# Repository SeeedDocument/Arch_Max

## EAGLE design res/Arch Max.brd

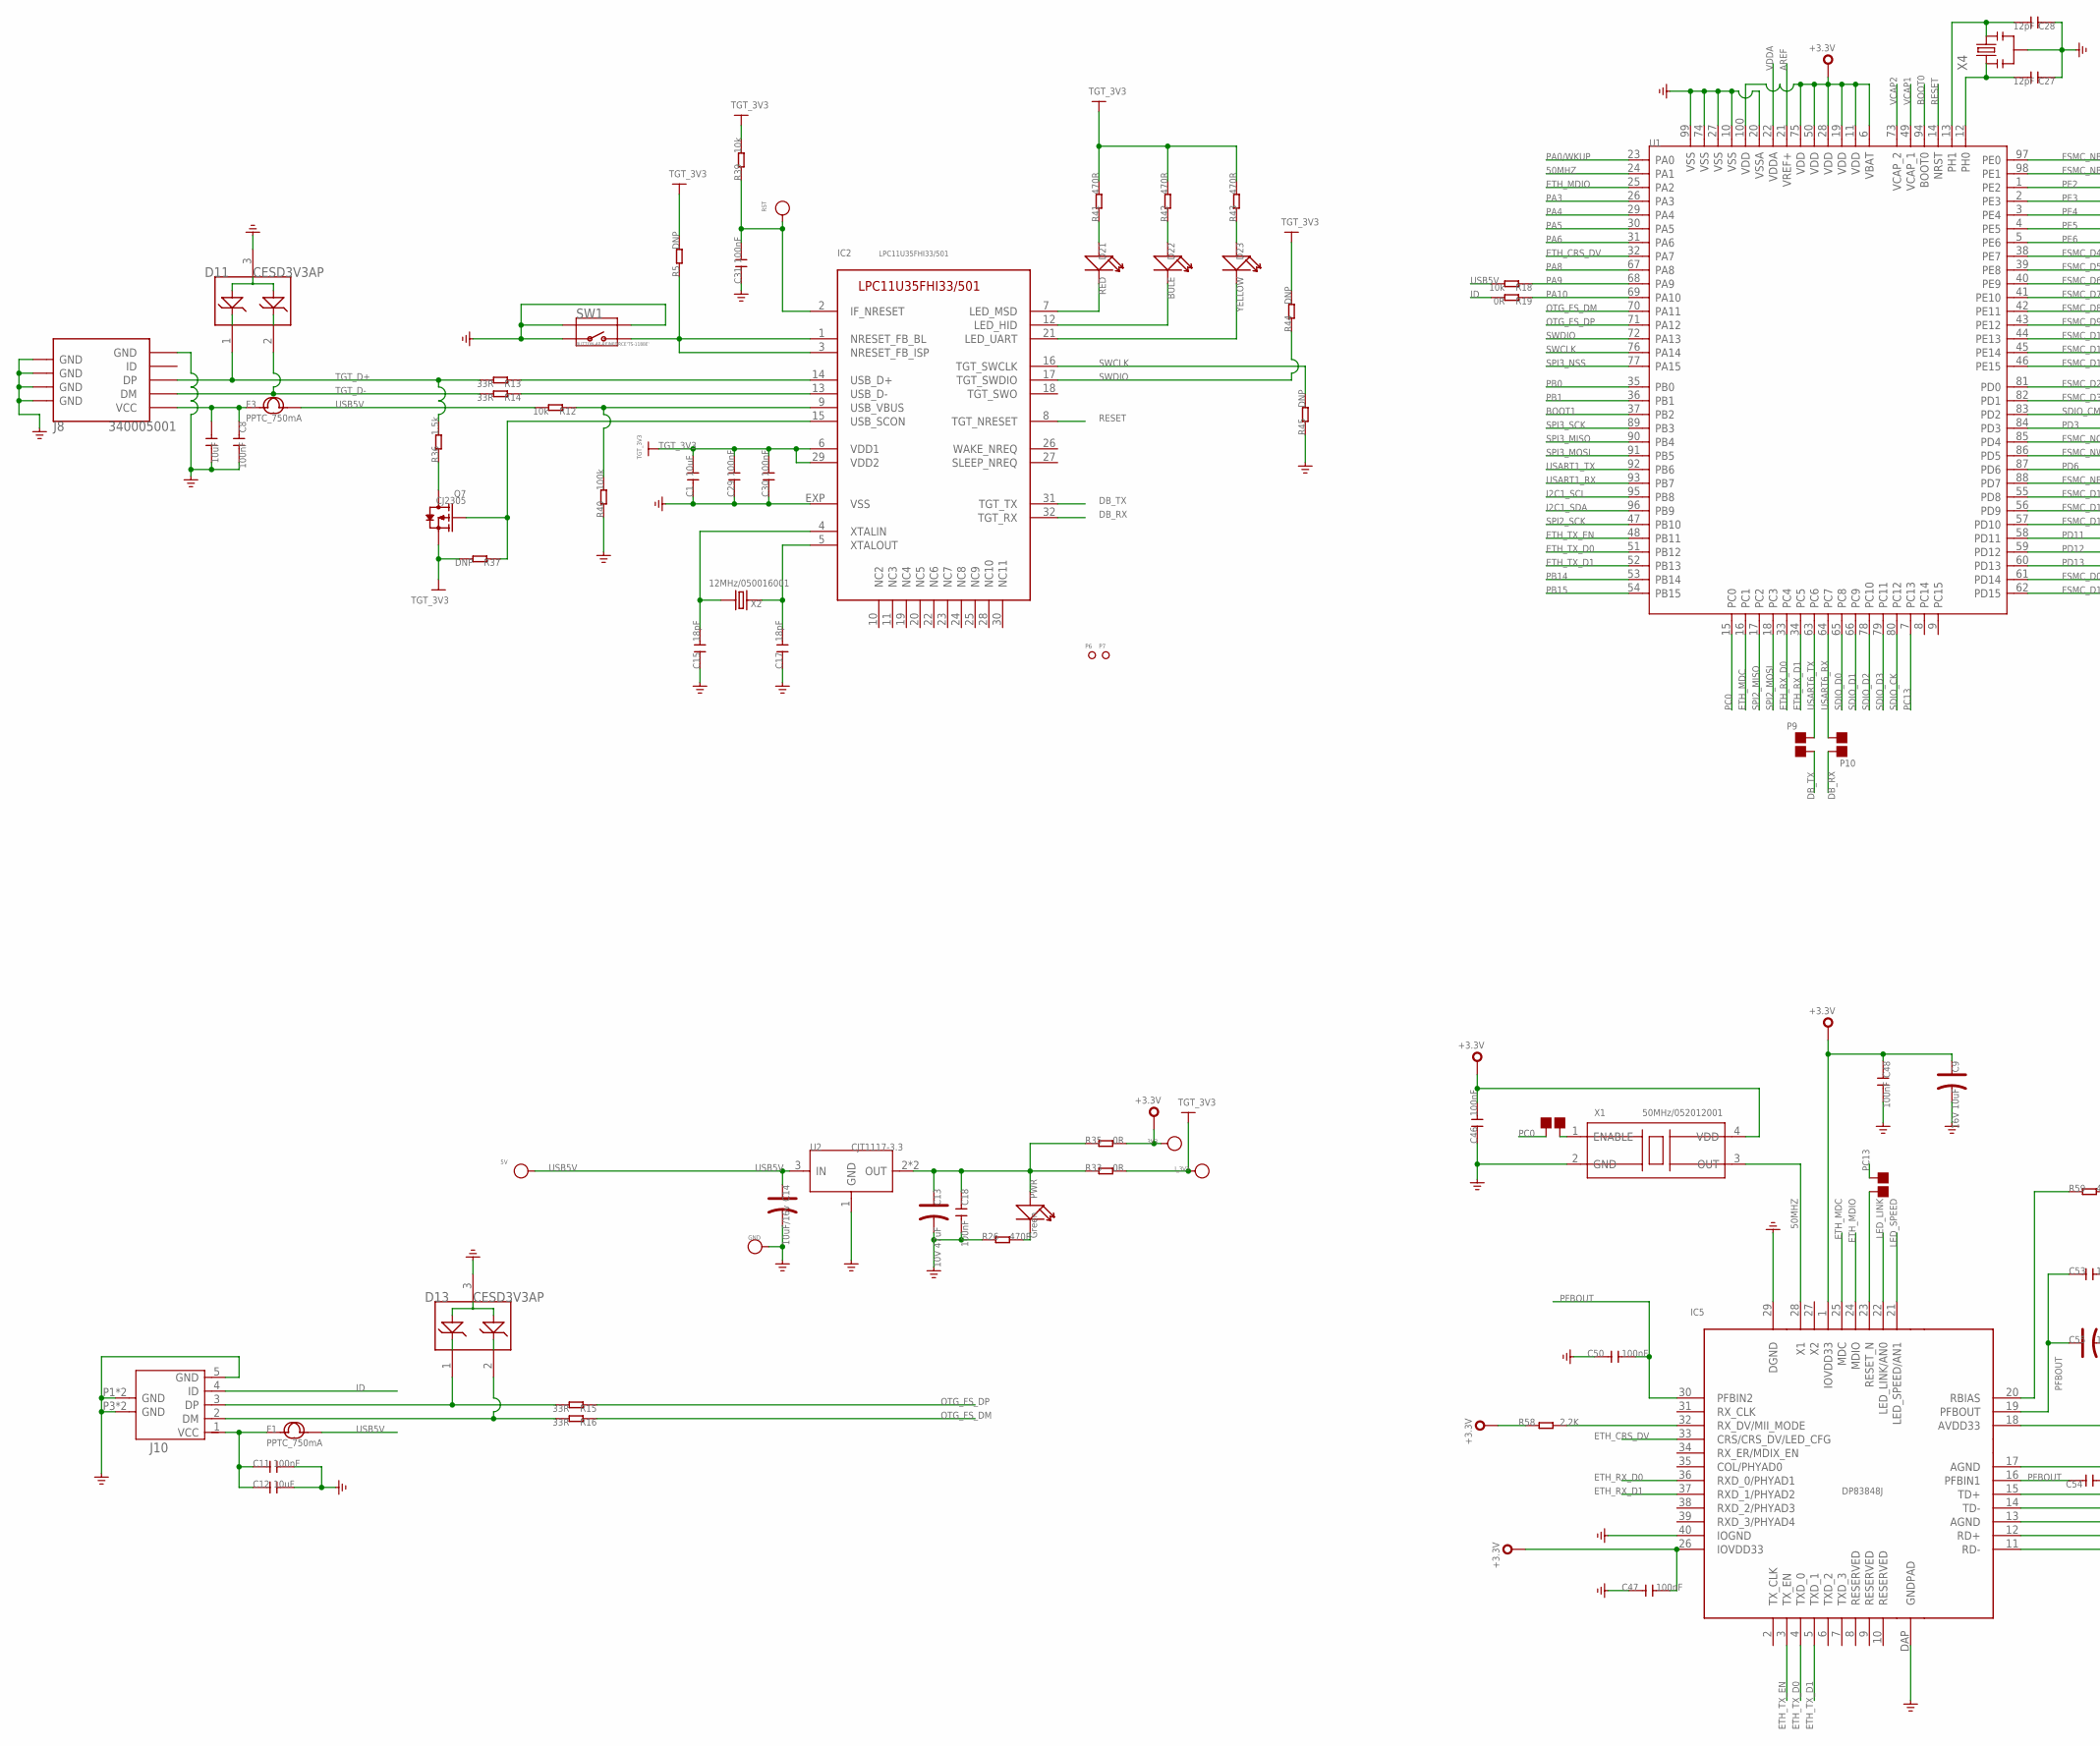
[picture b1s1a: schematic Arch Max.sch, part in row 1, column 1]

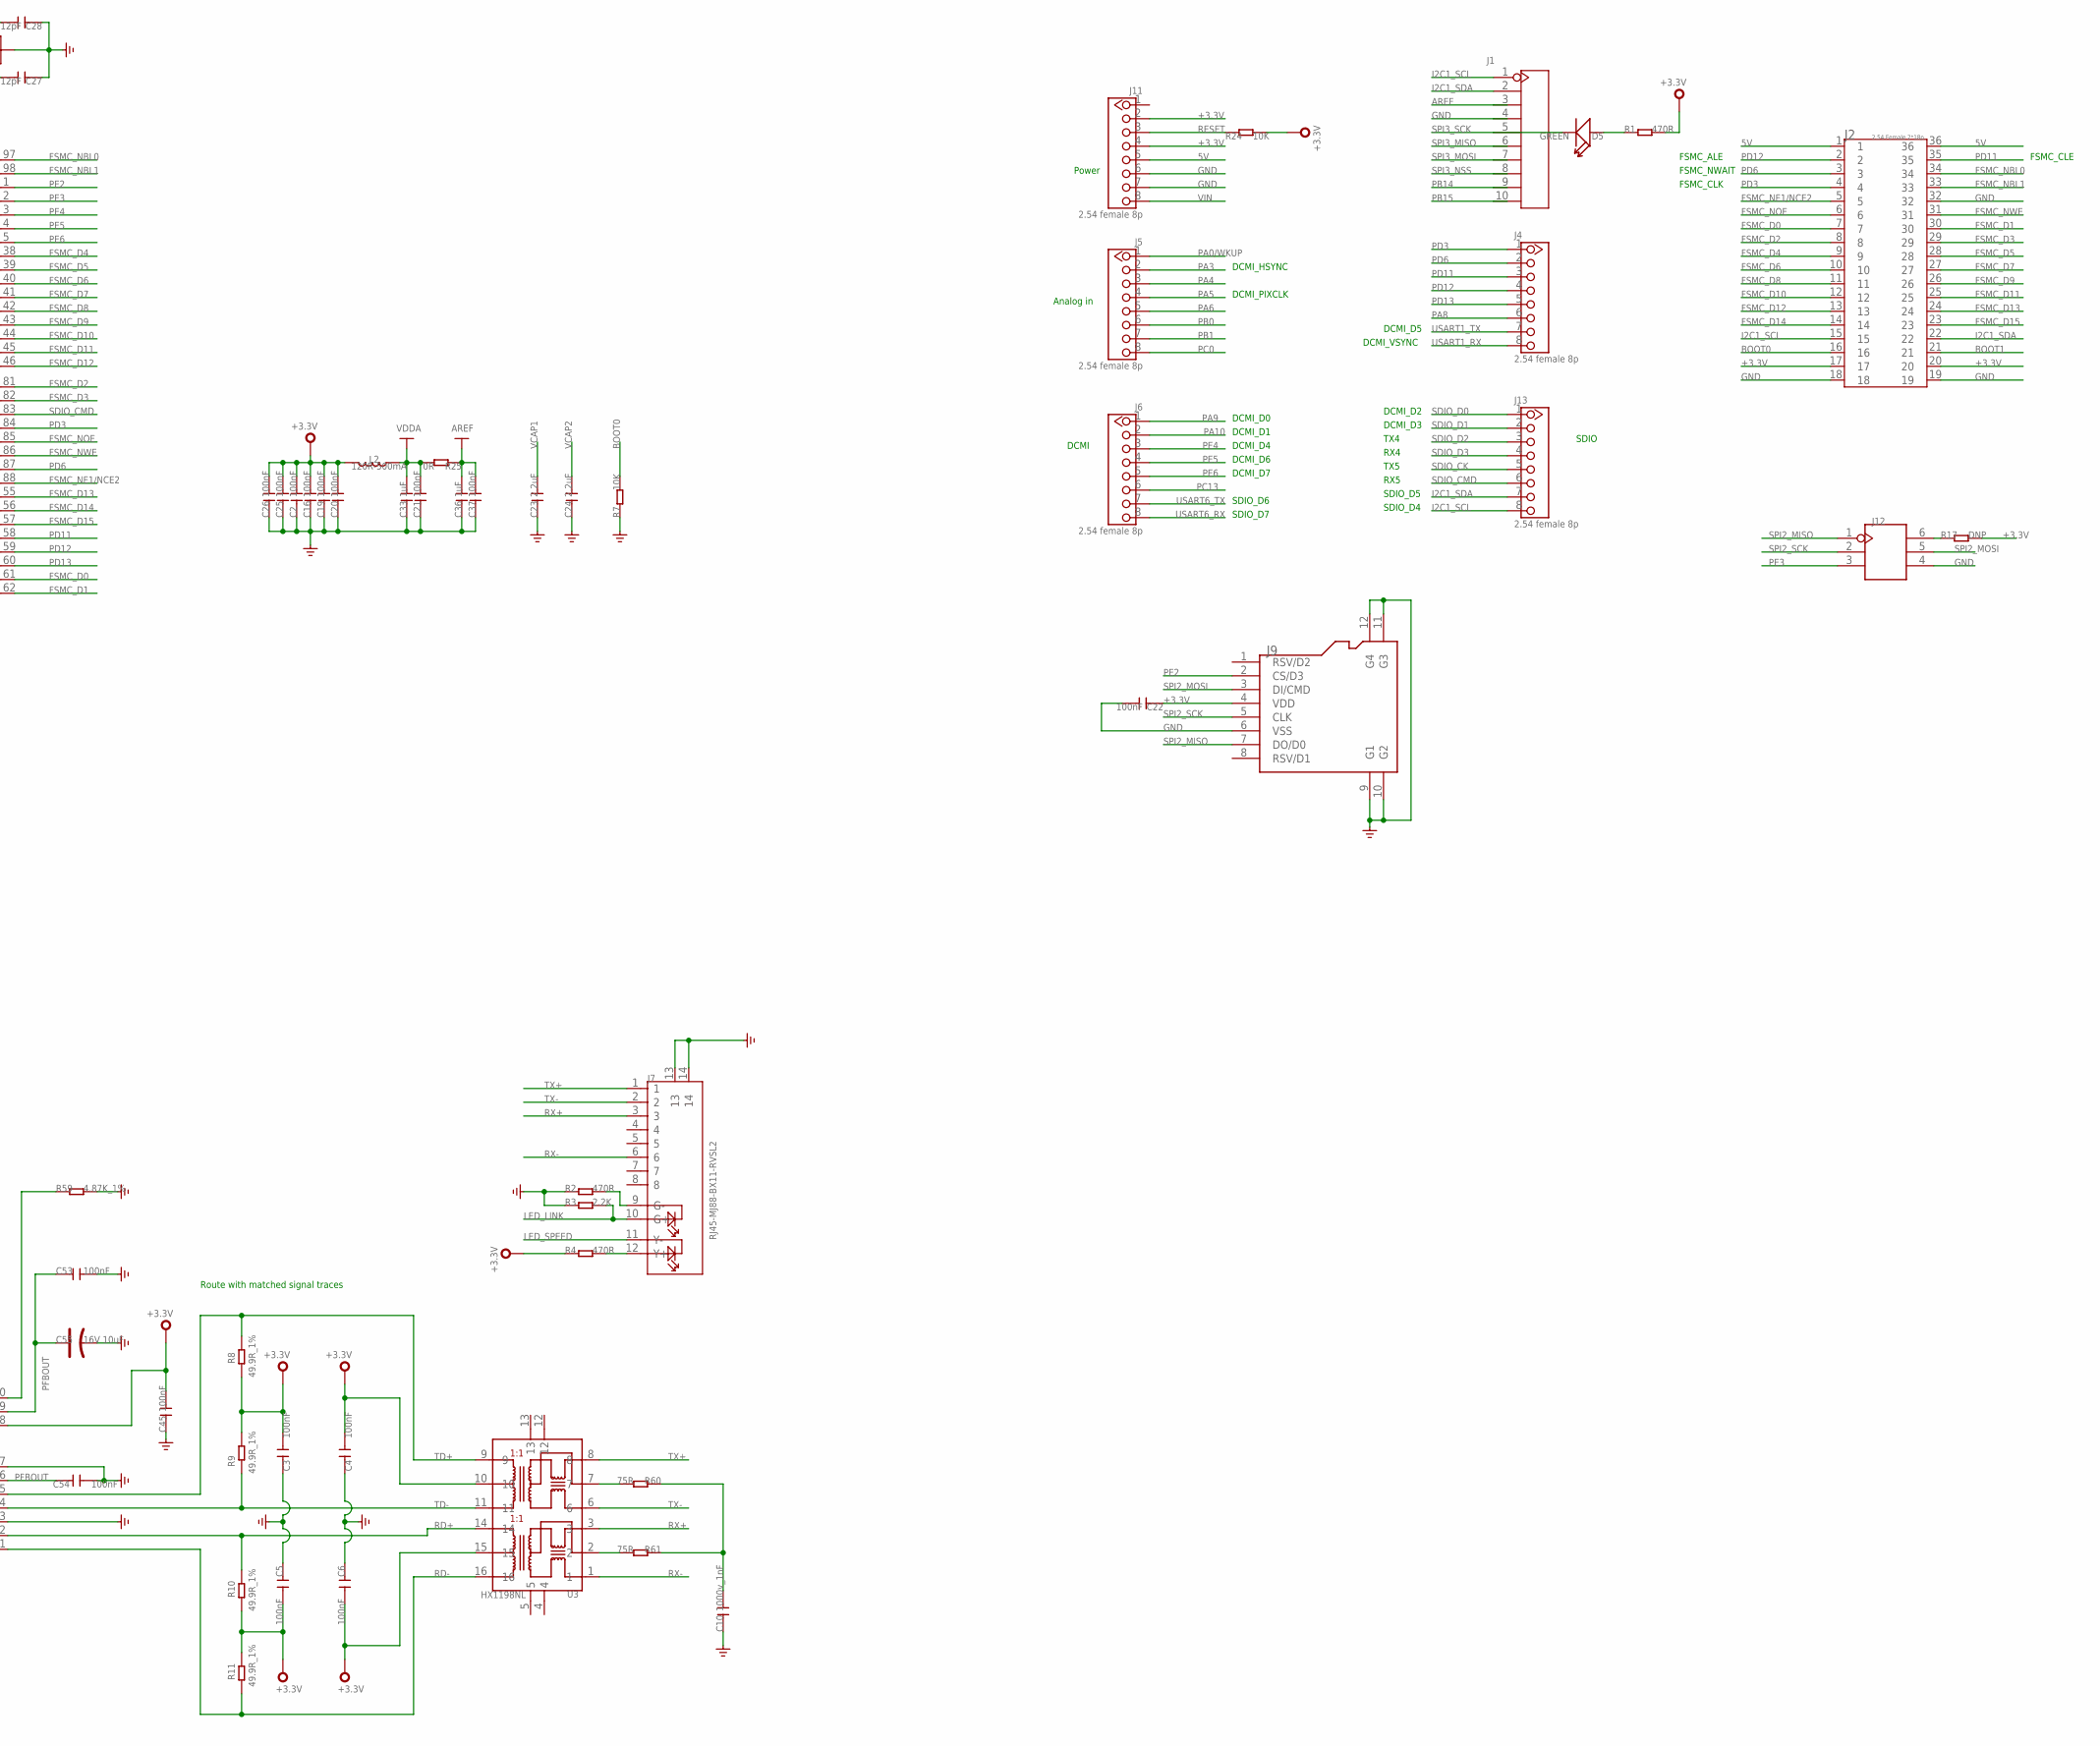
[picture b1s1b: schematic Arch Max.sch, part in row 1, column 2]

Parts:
3V3, 5V: PAD-TEST-POINT'4545'; TP_4545
C1, C7, C12: 10uF; C0805
C2, C3, C4, C5, C6, C8, C11, C16, C18, C19, C20, C21, C22, C25, C26, C29, C30, C31, C37, C45, C46, C47, C48, C50, C53, C54: 100nF; C0603
C9, C55: 16V 10uF; AVX-A
C10: 1000v_1nF; C1206
C13: 10V 47uF; AVX-B
C14: 10uF/16v; AVX-A
C15, C17: 18pF; C0603
C23, C24: 2.2uF; C0603
C27, C28: 12pF; C0603
C33, C36: 1uF; C0603
D5: GREEN; LED-0603
D11, D13: CESD3V3AP; SOT23
D21: RED; LED-0603
D22: BULE; LED-0603
D23: YELLOW; LED-0603
F1, F3: PPTC_750mA; F1206
GND: PAD-TEST-POINT'4545'; TP_4545
IC2: LPC11U35FHI33/501; MBED-ICS_HVQFN33
IC5: DP83848J; LLP-40
I_3V3: PAD-TEST-POINT'4545'; TP_4545
J1: HEADER-10P-2.54; 10P-2.54-65/35MIL
J2: 2.54 Female 2*18p; 2.54-2X18P
J4, J5, J6, J11, J13: 2.54 female 8p; CK_1X8
J7: RJ45-MJ88-BX11-RVSL2
J8: 340005001; MICRO-USB
J9: HOLDER-MICROSD-8P; 8P-SMD
J10: USB-MICRO-5P'AB'; MICRO-USB-5P-AB
J12: HEADER-2X3P-65/35MIL; 2X3P-2.54-65/35MIL
L2: 120R-500mA; L0603
P1, P5, P9, P10: PAD-JUMPER-2P; 2P-SMD-1.78X1.27
P6, P7: PAD-MARK'ANNULAR'; ROUND-MARK-1.0
PWR: Green; LED-0603
Q7: CJ2305; SOT23
R1, R2, R4, R26, R41, R42, R43: 470R; R0603
R3, R58: 2.2K; R0603
R5, R17, R37, R44, R45: DNP; R0603
R7, R24: 10K; R0603
R8, R9, R10, R11: 49.9R_1%; R0603
R12, R18, R39: 10k; R0603
R13, R14, R15, R16: 33R; R0603
R19, R25, R33, R35: 0R; R0603
R36: 1.5k; R0603
R40: 100k; R0603
R59: 4.87K_1%; R0603
R60, R61: 75R; R0603
RST: PAD-TEST-POINT'4545'; TP_4545
SW1: BUTTON-4P-REINFORCE'TS-1188E'; 4P-SMD-7X3.5X3.5H
U1: STM32F407VET6; LQFP100
U2: CJT1117-3.3; SOT-223
U3: HX1198NL; SOIC16-9.53
X1: 50MHz/052012001; 4P-SMD-5X3.2
X2: 12MHz/050016001; 2P-SMD-5X3.2
X4: CRYSTAL-RESONATOR'SMD'; 3P-SMD-3.6X1.3

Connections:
5V: J2.1, J2.36, J11.5
50MHZ: IC5.28 (X1), U1.24 (PA1), X1.3 (OUT)
+3.3V: 3V3.T, C2.2, C3.1, C4.1, C5.1, C6.1, C9.+, C16.2, C19.2, C20.2, C22.1, C25.2, C26.2, C45.2, C46.2, C47.1, C48.1, IC5.1 (IOVDD33), IC5.18 (AVDD33), IC5.26 (IOVDD33), J2.17, J2.20, J9.4 (VDD), J11.2, J11.4, L2.2, R1.2, R4.1, R8.1, R9.2, R10.1, R11.2, R17.2, R24.2, R35.1, R58.1, U1.6 (VBAT), U1.11 (VDD), U1.19 (VDD), U1.28 (VDD), U1.50 (VDD), U1.75 (VDD), U1.100 (VDD), U3.10, U3.15, X1.4 (VDD)
AREF: C36.2, C37.2, J1.3, R25.1, U1.21 (VREF+)
BOOT0: J2.16, R7.2, U1.94 (BOOT0)
BOOT1: J2.21, U1.37 (PB2)
DB_RX: IC2.32 (TGT_RX), P10.2
DB_TX: IC2.31 (TGT_TX), P9.1
ETH_CRS_DV: IC5.33 (CRS/CRS_DV/LED_CFG), U1.32 (PA7)
ETH_MDC: IC5.25 (MDC), U1.16 (PC1)
ETH_MDIO: IC5.24 (MDIO), U1.25 (PA2)
ETH_RX_D0: IC5.36 (RXD_0/PHYAD1), U1.33 (PC4)
ETH_RX_D1: IC5.37 (RXD_1/PHYAD2), U1.34 (PC5)
ETH_TX_D0: IC5.4 (TXD_0), U1.51 (PB12)
ETH_TX_D1: IC5.5 (TXD_1), U1.52 (PB13)
ETH_TX_EN: IC5.3 (TX_EN), U1.48 (PB11)
FSMC_D0: J2.7, U1.61 (PD14)
FSMC_D1: J2.30, U1.62 (PD15)
FSMC_D2: J2.8, U1.81 (PD0)
FSMC_D3: J2.29, U1.82 (PD1)
FSMC_D4: J2.9, U1.38 (PE7)
FSMC_D5: J2.28, U1.39 (PE8)
FSMC_D6: J2.10, U1.40 (PE9)
FSMC_D7: J2.27, U1.41 (PE10)
FSMC_D8: J2.11, U1.42 (PE11)
FSMC_D9: J2.26, U1.43 (PE12)
FSMC_D10: J2.12, U1.44 (PE13)
FSMC_D11: J2.25, U1.45 (PE14)
FSMC_D12: J2.13, U1.46 (PE15)
FSMC_D13: J2.24, U1.55 (PD8)
FSMC_D14: J2.14, U1.56 (PD9)
FSMC_D15: J2.23, U1.57 (PD10)
FSMC_NBL0: J2.34, U1.97 (PE0)
FSMC_NBL1: J2.33, U1.98 (PE1)
FSMC_NE1/NCE2: J2.5, U1.88 (PD7)
FSMC_NOE: J2.6, U1.85 (PD4)
FSMC_NWE: J2.31, U1.86 (PD5)
GND: C1.1, C2.1, C3.2, C4.2, C5.2, C6.2, C7.2, C8.2, C9.-, C10.1, C11.2, C12.2, C13.-, C14.-, C15.1, C16.1, C17.1, C18.1, C19.1, C20.1, C21.1, C22.2, C23.1, C24.1, C25.1, C26.1, C27.1, C28.1, C29.1, C30.1, C31.1, C33.1, C36.1, C37.1, C45.1, C46.1, C47.2, C48.2, C50.2, C53.1, C54.1, C55.-, D11.3, D13.3, GND.T, IC2.EXP (VSS), IC5.13 (AGND), IC5.17 (AGND), IC5.29 (DGND), IC5.40 (IOGND), IC5.DAP (GNDPAD), J1.4, J2.18, J2.19, J2.32, J7.13, J7.14, J8.5 (GND), J8.S1 (GND), J8.S2 (GND), J8.S3 (GND), J8.S4 (GND), J8.S5 (GND), J8.S6 (GND), J9.6 (VSS), J9.9 (G1), J9.10 (G2), J9.11 (G3), J9.12 (G4), J10.5 (GND), J10.P1 (GND), J10.P2 (GND), J10.P3 (GND), J10.P4 (GND), J11.6, J11.7, J12.4, R2.1, R3.1, R7.1, R26.1, R40.1, R45.1, R59.2, SW1.1, SW1.S1, SW1.S2, U1.10 (VSS), U1.20 (VSSA), U1.27 (VSS), U1.74 (VSS), U1.99 (VSS), U2.1 (GND), X1.2 (GND), X4.2
GREEN: D22.-, IC2.12 (LED_HID)
GREEN1: D21.-, IC2.7 (LED_MSD)
I2C1_SCL: J1.1, J2.15, J13.8, U1.95 (PB8)
I2C1_SDA: J1.2, J2.22, J13.7, U1.96 (PB9)
ID: J10.4 (ID), R19.2
LED_LINK: IC5.22 (LED_LINK/AN0), J7.10 (G+), R3.2
LED_SPEED: IC5.21 (LED_SPEED/AN1), J7.11 (Y-)
unnamed: C11.1, C12.1, F1.1, J10.1 (VCC)
unnamed: J12.6, R17.1
unnamed: IC2.1 (NRESET_FB_BL), IC2.3 (NRESET_FB_ISP), R5.1, SW1.2
unnamed: IC5.23 (RESET_N), P1.2
unnamed: IC2.9 (USB_VBUS), R12.1, R40.2
unnamed: J7.9 (G-), R2.2
unnamed: J7.12 (Y+), R4.2
unnamed: D5.+, R1.1
unnamed: P5.2, X1.1 (ENABLE)
unnamed: C7.1, C8.1, F3.1, J8.1 (VCC)
unnamed: IC2.14 (USB_D+), R13.1
unnamed: IC2.13 (USB_D-), R14.1
unnamed: D13.1, J10.3 (DP), R15.2
unnamed: PWR.-, R26.2
unnamed: D13.2, J10.2 (DM), R16.2
unnamed: C13.+, C18.2, PWR.+, R33.1, R35.2, U2.2 (OUT), U2.TER (OUT)
unnamed: C31.2, IC2.2 (IF_NRESET), R39.1, RST.T
unnamed: IC2.15 (USB_SCON), Q7.1 (G), R37.1
unnamed: D22.+, R42.1
unnamed: Q7.3 (D), R36.1
unnamed: D21.+, R41.1
unnamed: D23.-, IC2.21 (LED_UART)
unnamed: D23.+, R43.1
unnamed: C15.2, IC2.4 (XTALIN), X2.2
unnamed: C17.2, IC2.5 (XTALOUT), X2.1
unnamed: R61.2, U3.2
unnamed: R60.2, U3.7
unnamed: C10.2, R60.1, R61.1
unnamed: IC5.20 (RBIAS), R59.1
unnamed: IC5.32 (RX_DV/MII_MODE), R58.2
OTG_FS_DM: R16.1, U1.70 (PA11)
OTG_FS_DP: R15.1, U1.71 (PA12)
PA0/WKUP: J5.1, U1.23 (PA0)
PA3: J5.2, U1.26 (PA3)
PA4: J5.3, U1.29 (PA4)
PA5: J5.4, U1.30 (PA5)
PA6: J5.5, U1.31 (PA6)
PA8: J4.6, U1.67 (PA8)
PA9: J6.1, R18.1, U1.68 (PA9)
PA10: J6.2, R19.1, U1.69 (PA10)
PB0: J5.6, U1.35 (PB0)
PB1: J5.7, U1.36 (PB1)
PB14: J1.9, U1.53 (PB14)
PB15: J1.10, U1.54 (PB15)
PC0: J5.8, P5.1, U1.15 (PC0)
PC13: J6.6, P1.1, U1.7 (PC13)
PD3: J2.4, J4.1, U1.84 (PD3)
PD6: J2.3, J4.2, U1.87 (PD6)
PD11: J2.35, J4.3, U1.58 (PD11)
PD12: J2.2, J4.4, U1.59 (PD12)
PD13: J4.5, U1.60 (PD13)
PE2: J9.2 (CS/D3), U1.1 (PE2)
PE3: J12.3, U1.2 (PE3)
PE4: J6.3, U1.3 (PE4)
PE5: J6.4, U1.4 (PE5)
PE6: J6.5, U1.5 (PE6)
PFBOUT: C50.1, C53.2, C54.2, C55.+, IC5.16 (PFBIN1), IC5.19 (PFBOUT), IC5.30 (PFBIN2)
RD+: IC5.12 (RD+), R10.2, U3.14
RD-: IC5.11 (RD-), R11.1, U3.16
RESET: IC2.8 (TGT_NRESET), J11.3, R24.1, U1.14 (NRST)
RX+: J7.3, U3.3
RX-: J7.6, U3.1
SDIO_CK: J13.5, U1.80 (PC12)
SDIO_CMD: J13.6, U1.83 (PD2)
SDIO_D0: J13.1, U1.65 (PC8)
SDIO_D1: J13.2, U1.66 (PC9)
SDIO_D2: J13.3, U1.78 (PC10)
SDIO_D3: J13.4, U1.79 (PC11)
SPI2_MISO: J9.7 (DO/D0), J12.1, U1.17 (PC2)
SPI2_MOSI: J9.3 (DI/CMD), J12.5, U1.18 (PC3)
SPI2_SCK: J9.5 (CLK), J12.2, U1.47 (PB10)
SPI3_MISO: J1.6, U1.90 (PB4)
SPI3_MOSI: J1.7, U1.91 (PB5)
SPI3_NSS: J1.8, U1.77 (PA15)
SPI3_SCK: D5.-, J1.5, U1.89 (PB3)
SWCLK: IC2.16 (TGT_SWCLK), R45.2, U1.76 (PA14)
SWDIO: IC2.17 (TGT_SWDIO), R44.1, U1.72 (PA13)
TD+: IC5.15 (TD+), R8.2, U3.9
TD-: IC5.14 (TD-), R9.1, U3.11
TGT_3V3: C1.2, C29.2, C30.2, IC2.6 (VDD1), IC2.29 (VDD2), I_3V3.T, Q7.2 (S), R5.2, R33.2, R37.2, R39.2, R41.2, R42.2, R43.2, R44.2
TGT_D+: D11.1, J8.3 (DP), R13.2, R36.2
TGT_D-: D11.2, J8.2 (DM), R14.2
TX+: J7.1, U3.8
TX-: J7.2, U3.6
USART1_RX: J4.8, U1.93 (PB7)
USART1_TX: J4.7, U1.92 (PB6)
USART6_RX: J6.8, P10.1, U1.64 (PC7)
USART6_TX: J6.7, P9.2, U1.63 (PC6)
USB5V: 5V.T, C14.+, F1.2, F3.2, R12.2, R18.2, U2.3 (IN)
VCAP1: C23.2, U1.49 (VCAP_1)
VCAP2: C24.2, U1.73 (VCAP_2)
VDDA: C21.2, C33.2, L2.1, R25.2, U1.22 (VDDA)
VIN: J11.8
XTALIN: C27.2, U1.12 (PH0), X4.1
XTALOUT: C28.2, U1.13 (PH1), X4.3

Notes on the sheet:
Route with matched signal traces
DCMI_D0
DCMI_D1
DCMI_D2
DCMI_D3
DCMI_D4
DCMI_D6
DCMI_D7
DCMI_D5
DCMI_HSYNC
DCMI_PIXCLK
DCMI_VSYNC
SDIO_D5
SDIO_D4
TX5
RX5
TX4
RX4
SDIO_D6
SDIO_D7
Analog in
FSMC_CLE
FSMC_ALE
FSMC_NWAIT
FSMC_CLK
Power
DCMI
SDIO

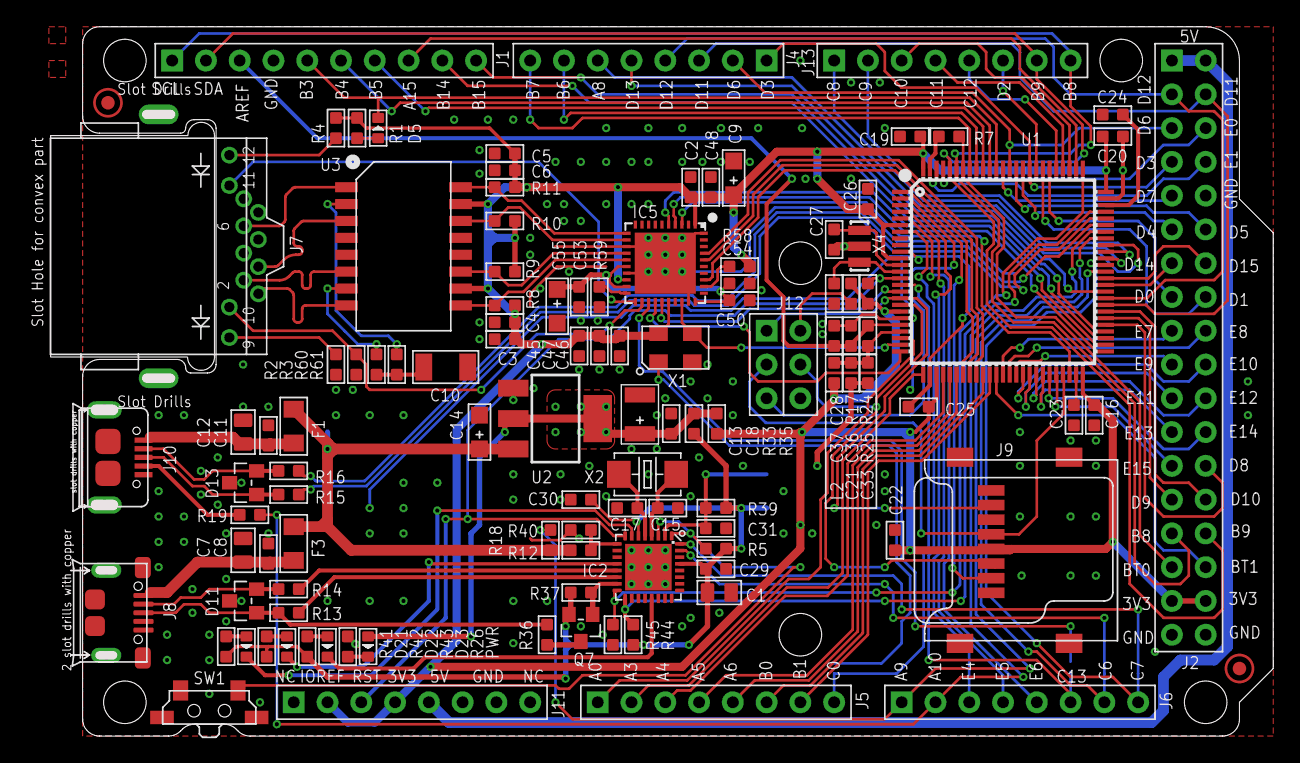
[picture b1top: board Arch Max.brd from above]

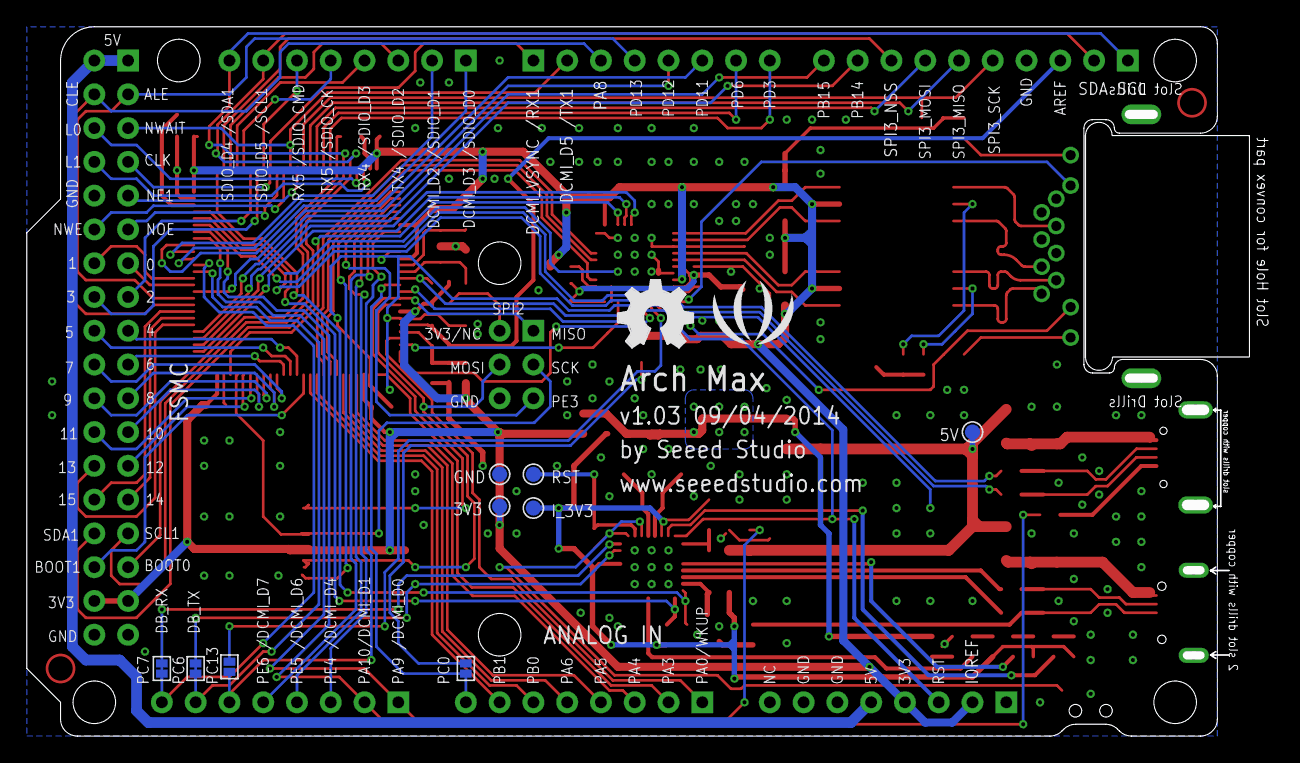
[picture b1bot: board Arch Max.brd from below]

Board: 2 copper layers, 91.9 x 53.3 mm, 123 parts (11 on the bottom side), 139 nets.

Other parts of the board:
U$1: OSHW_FILLX200_NOTEXT
U$4: LOGO_SILK

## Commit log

2017-06-07 upgrade
